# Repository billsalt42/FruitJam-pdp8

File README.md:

# PDP-8/E emulator for the Adafruit Fruit Jam

This turns an [Adafruit Fruit Jam](https://www.adafruit.com/product/6200) (RP2350B) into a
PDP-8/E minicomputer. It runs **OS/8** from RK05 cartridge-disk, DECtape or floppy images on the microSD card, or
the **TSS/8** time-sharing system with up to five users logged in at once. It also runs
two time-sharing systems built on OS/8, **MULTOS/8** and **ETOS**, if you supply their disk packs. TSS/8 comes in two
versions: DEC's TSS/8.24, and **UWM TSS/8.25** from the University of Wisconsin–Milwaukee, which
is assembled from source (see [`uwm/`](uwm/README.md)).
Output goes to an HDMI/DVI monitor as an 80×30 green-screen terminal. You type on a USB keyboard,
or connect from a computer over the USB-C serial ports.

```
Adafruit Fruit Jam PDP-8/E - OS/8 V3D - KBM V3Q - CCL V1F
Configured on 2026.09.24 at 17:53:24 PDT

Restart address = 07600

Type:
    .DIR                -  to get a list of files on DSK:
    .DIR SYS:           -  to get a list of files on SYS:
    .R PROGNAME         -  to run a system program
    .HELP FILENAME      -  to type a help file

.
```

## What is emulated

| Unit | Notes |
|---|---|
| PDP-8/E CPU, 32K words | Full instruction set, interrupts, KM8E memory extension (including user-mode traps) |
| KE8E EAE | Mode A and mode B (MUY, DVI, NMI, shifts, DAD, DST, DPIC, DCM, SAM, …) |
| KL8E console (03/04) | Keyboard and screen. The KSR mark bit is set on input. |
| RK8E + 4 × RK05 (74) | Disk images live on the microSD card. Uses the SIMH `.rk05` format, so PiDP-8/I and SIMH images work unchanged. |
| DK8-E line clock (13) | 60 Hz |
| LE8 line printer (66) | Output is appended to `printer.txt` on the SD card. |
| PC8E paper tape (01/02) | Reader input comes from `reader.bin` on the card; punch output is appended to `punch.bin`. |
| KL8E ×4 multiplexer (40–47) | TSS/8 terminals K01–K04. Each has its own virtual screen and USB serial port. |
| RF08 + RS08 (60–62, 64) | TSS/8 system disk (`tss8_rf.dsk`, 256K words). Blocks are cached in RAM and written back to the card. |
| TC08 + 4 × TU56 DECtape (76/77) | SIMH `.tu56` images (12-bit format). The tape moves with simulated acceleration and timing, block by block, as on the real drive. OS/8 can boot from DTA0. |
| RX8E + 2 × RX01 floppy (75) | SIMH `.rx01` images. An `.rx02` image switches to the RX28 controller (RX02 double density). OS/8 can boot from RXA0. |
| TSC8-75 (36) | The time-share board ETOS needs; fitted only while ETOS runs. |

The CPU is an independent C rewrite that follows SIMH's PDP-8 behaviour. It was checked against
SIMH with the same OS/8 and TSS/8 sessions and produced identical output (see [Testing](#testing)).

## What you need

* An Adafruit Fruit Jam
* A monitor or TV with HDMI input, and an HDMI cable
* A USB keyboard for one of the Fruit Jam's USB-A ports, or a computer running a terminal program
  on the USB-C port
* A microSD card formatted FAT32 or exFAT

## Quick start

1. **Flash the firmware.** Hold **Button 1** (BOOT) and tap **RESET**. A drive called `RP2350` appears.
   Copy `release/pdp8_fruitjam.uf2` onto it.
2. **Prepare the SD card.** Copy everything in the `sdcard/` folder to the root of the card:
   * `os8.rk05`: OS/8 V3D with BASIC, FORTRAN II/IV, PAL8, MACREL, TECO, U/W FOCAL, Adventure,
     BASIC games, Kermit-12 and more
   * `ock.rk05`: the OS/8 "Combined Kit" (V3D/V3F)
   * `blank.rk05`: an empty cartridge for your own files
   * `os8.tu56`: a bootable OS/8 V3F DECtape; `blank.tu56` and `blank.rx01`: an empty DECtape and floppy
   * `tss8_init.bin` and `tss8_rf.dsk`: DEC TSS/8.24 (the INIT loader tape and the RF08 system disk)
   * `uwm_init.bin` and `uwm_rf.dsk`: UWM TSS/8.25
   * `pdp8.cfg`: settings (optional)
3. Insert the card, connect the monitor and keyboard, and power up. During the 3-second countdown,
   press **O** for OS/8, **T** for DEC TSS/8 or **U** for UWM TSS/8. If you don't press anything, it boots the `system=`
   setting in `pdp8.cfg` (OS/8 out of the box). OS/8 comes up at the `.` prompt.

Updating from an earlier version: flash the new `.uf2`, and copy any `tss8_*`/`uwm_*`, `.tu56` or `.rx01` files you
don't have yet, plus the new `pdp8.cfg`, to the card. Your existing disk images keep working.

## Using it

| Key | Action |
|---|---|
| **F12** or **Button 1** | System menu: continue, boot OS/8 / TSS/8 / UWM TSS/8 / MULTOS/8 / ETOS, restart the OS/8 monitor at 07600, drives (I: swap disk, DECtape and floppy images, boot from tape or floppy), default system, keyboard case (K), speed, colour, save settings |
| **Alt-F1 … Alt-F5** | TSS/8: switch the monitor between the console (K00) and terminals K01–K04 |
| **F11** (or Alt-F6) | PDP-8/E front panel (lamps, switch register, console keys); F11 or Esc returns |
| Caps Lock | Toggles forced upper case (on by default, as on a Teletype; OS/8 commands must be upper case) |
| Backspace / Delete | RUBOUT (0177), which is OS/8's delete |
| Ctrl-C | Returns to the OS/8 monitor |
| Ctrl-O / Ctrl-U | Suppress output / delete the line |
| Arrow keys | VT52 cursor keys (ESC A/B/C/D) for TECO VTEDIT, KED, etc. |
| F1–F4 | VT52 PF1–PF4 |

**Serial ports:** the USB-C port shows up on your computer as **five** USB serial devices (for
example `/dev/ttyACM0`–`4`, `/dev/cu.usbmodem…`, or `COM` ports), named "PDP-8 Console K00" and
"TSS/8 Line K01"–"K04". Connect with any terminal program; the baud rate doesn't matter.
* The first port is the console. Everything on the console screen is copied to it, typing there
  works the same as on the keyboard, and **Ctrl-\\** opens the system menu.
* The other four are TSS/8 terminals K01–K04. They are only used while TSS/8 is running. Each one
  mirrors its virtual screen (Alt-F2 … Alt-F5), so several people can use TSS/8 from their own computers
  while someone else types on the Fruit Jam's keyboard.

**Screen:** the display is a VT52 with a few VT100 (ANSI) sequences added, so full-screen OS/8
editors work.

### A few things to try

```
.DIR                         list files on the system disk
.R BASIC                     BASIC  (NEW, give a name, type a program, RUN, BYE)
.EXECUTE HELLO.FT            compile and run a FORTRAN IV program (create it with EDIT or PIP)
.PAL PROG/L                  assemble PROG.PA with PAL8; .LOAD PROG / .START
.R UWF16K                    U/W FOCAL
.R FRTS  then  *ADVENT.LD<Esc>   Colossal Cave Adventure (press Enter at the three file prompts)
.R CHEKMO                    chess
.ZERO RKA1:                  initialise the first half of the disk in drive RK1 (blank.rk05)
.ZERO RKB1:                  ...and the second half
.COPY RKA1:<*.BA             copy files onto it
```

On OS/8 each RK05 cartridge appears as two devices: RKAn and RKBn for drive *n*.

### DECtapes and floppies

OS/8 sees the DECtape drives as **DTA0** and **DTA1** and the first floppy drive as **RXA0**. The
card comes with `os8.tu56` on DTA0 (a bootable OS/8 V3F system tape), a blank tape on DTA1 and a
blank floppy on RXA0:

```
.DIR DTA0:                   list the system tape
.ZERO DTA1:                  initialise the blank tape (also: ZERO RXA0:)
.COPY DTA1:<*.BA             copy files to it
.COPY RXA0:<DTA0:PIP.SV      ...or from tape to floppy
```

**F12 → I** (Drives) shows every drive. Keys 0–3 change RK0–RK3, 4–7 change DTA0–DTA3 and
8–9 change RXA0–RXA1. **N** in the image list makes a new blank `.tu56` or `.rx01` file. **B** boots
OS/8 from the DECtape in DTA0 and **F** from the floppy in RXA0. The choice is remembered for
**O**, and **W** saves it as `os8_boot`. DECtape images from SIMH, the PiDP-8/I project and
bitsavers (12-bit `.tu56`/`.dt8` format) work as they are. 16- and 18-bit DECtape images (from
PDP-11 or PDP-10 conversions) are not supported.

Tapes are read and written a block at a time. The block being worked on is written back when the
tape stops, and at least once a second.

### TSS/8

TSS/8 is DEC's time-sharing system for the PDP-8. It runs several users at once, each with their own
BASIC, FOCAL, FORTRAN, editor and files. To start it:

1. Press **T** at the boot countdown, or choose **T** in the F12 menu.
2. The console asks `LOAD, DUMP, START, ETC?`. Type `START`.
3. Enter the date as `M-D-YY` and the time as `HH:MM`, for example `9-25-84` and `09:35`. TSS/8.24
   only accepts years from 1974 to 1984, so pick a year in that range.
4. On any terminal, press Enter and then log in with `LOGIN 2 LXHE` (account 2, password LXHE).

```
.LOGIN 2 LXHE
TSS/8.24  JOB 01  [00,02]  K01    09:35:04
.SYSTAT                     who is logged in, free core and disk
.R CAT                      list your files
.R BASIC                    BASIC  (NEW / OLD, RUN, SAVE, BYE)
.R FOCAL                    FOCAL  (answer YES to keep LOG/EXP/ATN)
.R EDIT, .R FORT, .R PALD   editor, FORTRAN, PAL-D assembler
^B S                        stop the running program (Ctrl-B, then S)
.LOGOUT
```

**UWM TSS/8** is started the same way (press **U**). Two differences: it only lets you log in
with a **Ctrl-B** in front of `LOGIN`, and it prints a message of the day. See
[`uwm/README.md`](uwm/README.md) for how it was built and what was changed.

Switch between the console and K01–K04 with **Alt-F1 … Alt-F5**, or use the extra USB serial ports.
Five people can be logged in at once. The RF08 disk is cached in RAM and written back to
`tss8_rf.dsk` about once a second, so let it settle (LED off) before you power off. Keep a copy of the
original `tss8_rf.dsk` if you want to be able to start over.

### MULTOS/8

[MULTOS/8](http://www.pdp8online.com/) (Computer Methods, Salt Lake City, 1979) is time-sharing
built on OS/8. Each user runs ordinary OS/8 and its programs (BASIC, FOCAL,
PAL8, TECO and the rest), and has a slice of the RK05 as their own disk. It is not part of this
project, so get `multos8.rk05` from pdp8online.com and copy it to the card.

1. Press **M** at the boot countdown or in the F12 menu (or set `system=multos`). OS/8 boots
   from the MULTOS pack.
2. Recommended once: `COPY J2:<LOGOFF.SV,SYSTAT.SV,TIME.SV,TALK.SV`. This gives the second
   user their own copies of the MULTOS utilities, so `R LOGOFF` works for them.
3. `DATE 12-OCT-77` (OS/8 V3D only knows 1970–77), then `R MULTOS`, then the time as `hhmm`.
4. **Ctrl-H** logs on, on the console and on terminal K01 (Alt-F2, the second USB serial port,
   or SSH). `R LOGOFF` signs off; over SSH it also ends the session.

The pack as distributed is built for two terminals: the console, and K01 on the multiplexer at
device 40. In its `PARAM.PG`, `TERM2 EQU 32` means *octal* 40, because the PAGE8 assembler
reads plain numbers as decimal. Its clock shows a time a few hours on from the one you enter,
and runs slow. SIMH does exactly the same with this pack, so it comes from the software, not the
emulator. `tests/multostest.py` runs MULTOS/8 on the desktop build (set `MULTOS_RK`). It logs on
two users at once, runs BASIC on K01 while the console runs SYSTAT, and checks logging off and
SSH.

### ETOS

[ETOS](https://www.pdp8online.com/os/etos/etos.shtml) (Educational Data Systems, V5B 1978) gives
every user a virtual PDP-8 running unmodified OS/8. User programs run in the KM8-E's user mode, and
the monitor emulates their I/O. It also needs the **TSC8-75** time-share board, which traps JMP
and JMS in user mode so ETOS can follow field changes. The emulator has that board (after SIMH's
TSC device) and switches it on only for ETOS. Get `etosv5b-demo.rk05` from pdp8online.com and copy
it to the card.

1. Press **E** at the boot countdown or in the F12 menu (or set `system=etos`). OS/8 boots from
   the ETOS pack.
2. `R ETOS`, then answer `T` to `OPTION?` to start the time-sharing.
3. On the console and on K01 (Alt-F2, the second USB serial port, or SSH), press Enter for
   `?LOGIN PLEASE`, then type `LOGIN`. The demo's accounts are `0,4` (password `USER1`,
   privileged) and `0,5` (`USER2`).
4. `^V S` Enter gives the ETOS monitor's `!` prompt, for commands such as `SYSTAT` and `LOGOUT`.
   Over SSH, `LOGOUT` also ends the session. If you just close the window, the Fruit Jam logs the
   job out (Ctrl-C, `^V S`, `LOGOUT`).

The demo pack is configured for two terminals, the console and K01. Typing on K02–K04 hangs
it, on SIMH too, so leave `etos_lines=1`. Its clock isn't set, so it shows 1 January 1975.
`tests/etostest.py` (set `ETOS_RK`) logs in two users, runs BASIC golf on K01 while the console runs
its own BASIC program and SYSTAT, and checks LOGOUT and SSH. The same steps give the same output
on SIMH with `set tsc enabled`.

### Front panel

Press **F11** for a PDP-8/E-style front panel. The machine keeps running while you watch it.

* **Lamps:** EMA + MEMORY ADDRESS (15 lamps), a 12-bit register display, and RUN and ION. The
  **Up/Down** keys turn the selector to STATUS, AC (with the link lamp), MD, MQ or IR. While the
  panel is on screen, the CPU samples its registers every few dozen instructions. Each lamp's
  brightness follows how often it was lit, and fades a little like an incandescent bulb, so the
  familiar idle-loop and swapping patterns show up.
* **Switch register:** the number-row keys **1 2 3 … 9 0 - =** flip switches 0–11. **O** followed by
  four octal digits sets them all at once, and **Z** clears them. Programs read the switches with
  `OSR`.
* **Console keys:** **H** HALT, **G** CONT, **S** SING STEP, **L** ADDR LOAD (PC and console address
  ← switches), **X** EXTD ADDR LOAD (IF ← switches 6–8, DF ← 9–11), **E** EXAM, **D** DEP (store the
  switches and advance) and **C** CLEAR. Like the real console, EXAM/DEP/ADDR LOAD/CLEAR/SING STEP
  only work while the machine is halted.

Toggling in a program the 1970s way looks like this. Press H, then O0200 and L to set the address.
Then, for each word, O and four octal digits followed by D to deposit it. Finally O0200, L and G to
run it.

### Terminals over WiFi (SSH)

The Fruit Jam's ESP32-C6 WiFi coprocessor lets people log in to the PDP-8 with an ordinary `ssh`
client, from Mac, Linux or Windows. Under TSS/8 each SSH login gets one of the terminal lines
K01–K04, so up to four people can share the machine over the network. Under MULTOS/8 and ETOS it
gets one of the lines they were built for. Under OS/8 it gets the console.

1. In `PDP8.CFG` set `wifi_ssid`, `wifi_password` and `ssh_password` (all SSH users share this one
   password), and restart.
2. The F12 menu shows the address, for example `SSH: WiFi "home": ssh 192.168.1.40`, and the host key
   fingerprint. The first time you connect, `ssh` shows the same fingerprint and asks you to confirm it.
3. `ssh 192.168.1.40`, then enter the SSH password. You'll see
   `[PDP-8 on Fruit Jam: connected to line K02 of TSS/8]`. Press Enter and log in to TSS/8 as usual,
   for example `LOGIN 2 LXHE`, or `^B LOGIN 2 LXHE` under UWM.

The SSH user name picks the line: `k01` … `k04` for a particular TSS/8 line, `k00` (or `console`)
for the console, and anything else for the first free line. A line whose USB serial port is open
counts as busy. TSS/8's `LOGOUT` ends the SSH session, like a modem hanging up. If you just close the
window instead, the Fruit Jam logs that job out for you (`^B S`, then `LOGOUT`) so the next person
on that line starts fresh.

The server only speaks the modern algorithms all current clients use: curve25519 key exchange, an
Ed25519 host key, and chacha20-poly1305 encryption. It runs on the Fruit Jam's main processor, and
the WiFi chip only carries the network connections, so its standard nina-fw firmware is used as it
comes. The host key is created on first use and kept in `SSHKEY.BIN` on the card. Delete that
file to make a new key. TSS/8's own passwords are 1970s-grade, so keep this on your home
network, not open to the internet.

### PiDP-8/I hardware panel

A real [PiDP-8/I](https://obsolescence.dev/pidp8i) panel can be connected too. A Raspberry Pi Pico 2
(or Pico) takes the place of the Raspberry Pi behind the panel and plugs into one of the Fruit Jam's
USB-A ports. Its lamps and switches then work with OS/8 and TSS/8, alongside the F11 screen. See
[`pidp8-panel/README.md`](pidp8-panel/README.md) for the wiring, firmware and switch functions. To
avoid the 26 jumper wires, [`hardware/pico-adapter`](hardware/pico-adapter/README.md) has a ready-to-order
adapter board (KiCad project and gerbers).

### Settings (`pdp8.cfg`)

```
system=os8          # what to boot at power-up: os8, tss8, uwm, multos or etos
rk0=os8.rk05        # disk images for drives 0-3 (files in the root of the card)
rk1=blank.rk05
rk2=ock.rk05
rk3=
dt0=os8.tu56        # TC08 DECtape images for DTA0-DTA3
dt1=blank.tu56
dt2=
dt3=
rx0=blank.rx01      # floppy images for RXA0-RXA1 (.rx01, or .rx02 for the RX28)
rx1=
os8_boot=rk         # OS/8 boots from rk (RK0), dectape (DTA0) or floppy (RXA0)
tss8_bin=tss8_init.bin   # TSS/8 INIT tape (BIN format)
tss8_rf=tss8_rf.dsk      # TSS/8 RF08 disk image (SIMH format)
uwm_bin=uwm_init.bin     # UWM TSS/8.25 INIT tape
uwm_rf=uwm_rf.dsk        # UWM TSS/8.25 RF08 disk image
color=green         # green, amber, white, blue
uppercase=on        # fold keyboard input to upper case
speed=full          # full = as fast as the RP2350 can go; real = ~400K instr/s like an 8/E
autoboot=3          # seconds before booting; -1 waits for Enter
wifi_ssid=          # WiFi network for SSH (empty = WiFi off)
wifi_password=
ssh_password=       # the one password for SSH logins (SSH stays off while empty)
ssh_port=22
hostname=pdp8       # name the Fruit Jam gives the WiFi router
multos_rk=multos8.rk05   # MULTOS/8 pack, booted with M (not included)
multos_lines=1      # terminals besides the console that MULTOS/8 was built for
etos_rk=etosv5b-demo.rk05   # ETOS pack, booted with E (not included)
etos_lines=1        # terminals besides the console that ETOS was configured for
```

Values can't contain `#`, because everything after it is treated as a comment.

You can change all of these from the F12 menu, and **W** in that menu writes them back to the card.
If `os8.rk05` is missing, the first `*.rk05` file on the card is booted. An image shorter than a
full RK05 (for example one produced by SIMH) is padded with zeros to 3,325,952 bytes the first time
it is mounted.

Writes go straight to the image file on the card, and the file is synced after half a second without
disk activity. The on-board LED (GPIO29) lights while there are unsynced writes. Wait for it to go out before you
switch off.

## How it works

```
core 0: PDP-8/E CPU + devices ─ RK8E / RF08 ─► FatFs ─► SPI microSD (GPIO34-36, CS 39)
        TinyUSB host (PIO-USB, GPIO1/2, via the on-board hub) ─► keyboard
        TinyUSB device (native USB-C) ─► 5 CDC serial ports (K00-K04)
        5 virtual terminals (VT52/ANSI), one per PDP-8 terminal line
core 1: HSTX DVI 640x480@60 (GPIO12-19), scanlines rendered on the fly
        from the selected terminal's 80x30 character buffer with an 8x16 font
```

The clocks follow the approach of the Adafruit/Pimoroni DVHSTX driver. The system runs at 240 MHz
from the USB PLL, an exact multiple of 12 MHz, which PIO-USB needs. The system PLL is free to make the
exact 126 MHz HSTX clock (25.2 MHz pixels). The whole program runs from RAM (`copy_to_ram`).

```
core/        portable PDP-8/E emulator (pdp8.c/.h); no hardware dependencies
firmware/    Fruit Jam firmware (Pico SDK): main, video, terminal, front panel, keyboard, SD card, USB,
             PiDP-8/I panel link
pidp8-panel/ firmware for the Pico 2 / Pico that drives a PiDP-8/I panel, wiring guide, test tool
net/         SSH server (ssh.c), SSH sessions as terminal lines (sshsrv.c), ESP32 nina-fw driver
             (nina.c) and WiFi/listener state machine (wifi.c); portable, also used by the host build
hardware/    pico-adapter: PiDP-8/I <-> Pico adapter board (KiCad 7 project, gerbers, generator scripts)
lib/monocypher  Monocypher 4.0.3 (X25519, Ed25519, ChaCha20, Poly1305)
host/        Linux/macOS command-line build of the same core, used for testing
lib/         Pico-PIO-USB (MIT)
sdcard/      disk images + sample config for the microSD card
tests/       comparison tests against SIMH, and the UWM TSS/8 functional test
tools/       font converter, OS/8 image build script, palbart PDP-8 assembler
uwm/         UWM TSS/8.25 sources, patches and the script that builds uwm_rf.dsk
```

## Building from source

Firmware (needs Pico SDK 2.2 or newer, which has the `adafruit_fruit_jam` board, plus
`arm-none-eabi-gcc`):

```sh
git clone https://github.com/raspberrypi/pico-sdk
git -C pico-sdk submodule update --init lib/tinyusb
export PICO_SDK_PATH=$PWD/pico-sdk
make firmware            # -> pdp8_fruitjam.uf2
make panel               # -> pidp8_panel_pico2.uf2, pidp8_panel_pico.uf2 (PiDP-8/I interface)
```

Desktop build of the emulator, for trying OS/8 or TSS/8 in a terminal (Ctrl-E quits):

```sh
make host
cp sdcard/os8.rk05 /tmp/ && build/pdp8host /tmp/os8.rk05
cp sdcard/tss8_rf.dsk /tmp/ && build/pdp8host -tss8 /tmp/tss8_rf.dsk sdcard/tss8_init.bin 4000
#   ...then connect extra TSS/8 terminals with:  nc localhost 4000   (or telnet)
```

Rebuild the OS/8 disk images from the original DEC distribution DECtapes (this uses the PiDP-8/I
project's tools and SIMH): `tools/build-images.sh`. Rebuild UWM TSS/8 from its sources:
`make uwm`.

## Testing

`make test` runs the same scripted OS/8 and TSS/8 sessions on SIMH and on this core and compares the
transcripts. It needs a SIMH `pdp8` binary in `SIMH_PDP8` and Python `pexpect`. The sessions
cover:

* `DIR`, PIP file creation, CCL commands
* FORTRAN IV compile, load and run (`EXECUTE`), including trig, exp/log and integer loops
* PAL8 assembly, `LOAD` and `START` of the resulting program
* BASIC with floating-point functions and arrays, plus `SAVE`
* U/W FOCAL (interrupt-driven terminal I/O)
* `tests/eaetest.pa`: an EAE exerciser that checksums 512 random operand pairs through every
  mode A and mode B instruction
* TSS/8 (`tests/tss8test.py`): INIT start-up, date and time, login, `R CAT`, a BASIC prime sieve,
  FOCAL, `SYSTAT` and `LOGOUT` on the console. This exercises the RF08 disk, user-mode traps,
  swapping and the clock.

* PiDP-8/I panel logic (`tests/pidptest.c`, `make pidptest`). A program is toggled in and run
  from simulated switches (LOAD ADD, DEP, EXAM, START, STOP, SING INST + CONT). The test also checks
  the lamp frames, both halted and averaged while running, and the protocol's resynchronisation.
* SSH (`tests/sshtest.py`, `make sshtest`). These run DEC TSS/8.24 with real SSH clients: OpenSSH,
  plus asyncssh and Dropbear's `dbclient` when installed. They check the host key fingerprint and
  that three wrong passwords end the connection. Four sessions log in on K01–K04 and run BASIC at
  the same time, and a fifth is turned away. They also check that `k00` gets the console, that a
  long paste is flow-controlled without loss, and that `LOGOUT` hangs up. A dropped session's job
  must be logged out, the session must survive forced re-keying, and 30 connections of random
  junk must not stop the server accepting logins. Under OS/8, SSH must get the console. The
  same tests run a second time with the SSH traffic going through the nina-fw driver to a
  simulated ESP32 (`tests/fakeesp.c`). That simulation answers each command exactly as nina-fw's
  `CommandHandler.cpp` does, and rejects malformed command packets.
* DECtape and floppy (`tests/dtrxtest.py`). OS/8 on the RK05 zeroes a blank tape and a blank floppy,
  copies files to and between them, types and runs files from them, then deletes and SQUISHes on
  the tape. The transcripts match SIMH's, and so do the resulting tape and floppy images, byte for
  byte. OS/8 is also booted from a DECtape system tape and runs BASIC from it. The RX28/RX02 code is
  ported from SIMH line for line, but no RX02 OS/8 system was available to test it.
* UWM TSS/8.25 (`tests/uwmtest.py`). SIMH can't run this monitor unmodified (see
  [`uwm/README.md`](uwm/README.md)), so this is a functional test. It covers start-up, Ctrl-B login on
  the console and all four lines, the message of the day, BASIC on four lines at once, SYSTAT showing
  all five jobs, CAT, FOCAL and LOGOUT.

Except for the UWM test, all of these give identical output on SIMH and on this core. On the desktop build, all five TSS/8 terminals
(the console plus four multiplexer lines) were also logged in at once, with four of them running BASIC
programs at the same time.
Adventure, CHEKMO, a second RK05 drive
(`ZERO`/`COPY`/`DIR RKA1:`) and the OS/8 Combined Kit image were also run on the desktop build.

**Hardware status:** v1.0 (OS/8), v1.1 (DEC TSS/8, virtual terminals, extra USB serial ports) and
v1.2 (UWM TSS/8, paper tape) have been run on a real Fruit Jam. v1.3 adds the front panel. The
panel's drawing and console keys were checked on the desktop build, which produced the screenshot
above. It compiles cleanly for the RP2350 (about 117 KB of code and 162 KB of RAM) but has not yet
been run on the board. v1.4 adds the PiDP-8/I link. As of v1.4.2 it has been run on a real Fruit Jam
with an original Pico driving a PiDP-8/I panel, and its switch and lamp logic is also covered by
`pidptest`.
v1.5 adds SSH over WiFi, which has been run on a real Fruit Jam with UWM TSS/8 and SSH sessions
on all four terminal lines. v1.6 adds MULTOS/8 and v1.7 adds ETOS with the TSC8-75; both have also
been run on the board. v1.8 adds DECtape and floppy drives, tested on the desktop build against
SIMH; the firmware builds but hasn't been run on the board yet.

## Licences

* Emulator, firmware and tools: MIT. The CPU and device semantics follow SIMH (Robert M Supnik,
  MIT-style licence).
* HSTX DVI code: derived from pico-examples (BSD-3-Clause).
* Pico-PIO-USB: MIT. FatFs: ChaN's FatFs licence (see `firmware/fatfs/LICENSE.txt`).
* Monocypher (`lib/monocypher`): CC0 or BSD-2-Clause, your choice (`lib/monocypher/LICENCE.md`).
* Font: Spleen 8x16 by Frederic Cambus, BSD-2-Clause (`firmware/FONT-LICENSE-spleen.txt`).
* OS/8 and its utilities are DEC software, distributed under the DEC hobbyist licence in
  `sdcard/OS8-LICENSE.md` (non-commercial use). The disk images were built with the
  [PiDP-8/I](https://tangentsoft.com/pidp8i) project's tools.
* UWM TSS/8.25 sources: DEC TSS/8 as extended at the University of Wisconsin–Milwaukee
  (Richard Bartlein, 1974–76), from bitsavers and Brad Parker's cpus-pdp8 project. `uwm_rf.dsk`
  carries the DEC TSS/8.24 library file system. palbart (`tools/palbart`) is free software; its
  licence is included with it.
* The TSS/8.24 files (`tss8_init.bin`, `tss8_rf.dsk`) are the SIMH TSS/8 kit as redistributed by
  the PiDP-8/I project. That project describes their licensing as not fully settled but believed
  freely redistributable for hobby use (see its `COPYING.md`).

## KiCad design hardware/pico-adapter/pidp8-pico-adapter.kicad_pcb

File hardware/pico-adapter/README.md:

# PiDP-8/I ↔ Raspberry Pi Pico adapter board

This board replaces the 26 jumper wires between a PiDP-8/I and the Pico panel interface. It is
the size of a Raspberry Pi HAT (65 × 56.5 mm), with the Pi's four M2.5 mounting holes. Its
40-pin connector sits where the Pi's GPIO header would be, so it plugs into the PiDP-8/I exactly
where the Raspberry Pi did. The Pico (or Pico 2) is soldered to the **back**. Its USB connector
sticks out at one edge for the cable to the Fruit Jam, and its BOOTSEL button stays reachable.

| File | What it is |
|---|---|
| `pidp8-pico-adapter-gerbers.zip` | upload this to JLCPCB, PCBWay, OSH Park, etc. |
| `pidp8-pico-adapter-1to1.pdf` | print at 100 % to check the fit before ordering |
| `pidp8-pico-adapter-schematic.pdf` | schematic |
| `pidp8-pico-adapter.kicad_pcb` / `.kicad_sch` / `.kicad_pro` | KiCad 7 project, if you want to change it |
| `make_board.py`, `route.py`, `render.py`, `make_schematic.py`, `check_board.py` | the scripts that generate everything |

## Ordering

These are standard settings everywhere: 2 layers, 1.6 mm, any colour, HASL finish. The smallest
features are 0.25 mm tracks with 0.2 mm spacing and 0.35 mm vias, well within every cheap service.
At JLCPCB, five boards cost a few dollars plus shipping.

## Parts

| Ref | Part |
|---|---|
| J1 | 2×20 header, 2.54 mm. Use what a Raspberry Pi would present: normally a **male** pin header (the PiDP-8/I has the socket). If your PiDP-8/I has pins instead, use a 2×20 female socket. |
| U1 | Raspberry Pi Pico, Pico 2 (or the W versions), with two 1×20 male headers, or soldered flat by its castellations |
| JP1, JP2 | solder bridges (no parts) |
| — | 4 × M2.5 standoffs, as for the Pi (optional) |

## Assembly

1. **Jumpers first.** On the front, bridge the middle pad of JP1 and JP2 with a blob of solder:
   * to **STD** for a normal PiDP-8/I,
   * to **SER** if your PiDP-8/I has the serial-port modification (columns 10 and 11 then come
     from header pins 5 and 3 instead of 10 and 8; see `pidp8-panel/README.md`).

   Never bridge all three pads.
2. **J1 on the front** (the side with the jumpers and the big title). It faces the PiDP-8/I.
   Solder it on the back.
3. **The Pico on the back.** Match the silkscreen outline, with the USB connector at the board
   edge. Pin 1 is at the corner with the bevel. Solder on the front.
4. Flash `pidp8_panel_pico.uf2` or `pidp8_panel_pico2.uf2` (v1.2 or later), then plug the board
   into the PiDP-8/I in place of the Raspberry Pi. Don't fit both at once.

## How the firmware knows

The board ties the Pico's **GP28 to ground**. At start-up the panel firmware sees that and uses
this board's GPIO assignment, recorded in `pidp8-panel/board_map.h`. With GP28 left open, as when
hand-wired, it uses the original table from the panel README. One firmware file works both ways.

Each matrix line on the board goes to whichever Pico GPIO sits closest to its header pin, so the
tracks hardly cross. `make_board.py` makes that choice and writes `board_map.h` at the same time,
so the board and the firmware can't disagree. `check_board.py` then follows every connection on
the finished board, through the jumpers, and compares it with the PiDP-8/I's wiring as the pidp8i
software defines it and with `board_map.h`.

## Status

The board was generated, autorouted (Freerouting) and checked by script:
* KiCad's DRC reports no errors and no unconnected items. The only warnings are cosmetic: the Pico
  outline's USB tab overhangs the edge, and the footprints are generated rather than taken from a
  library.
* `check_board.py` passes.
* The gerbers were re-rendered with gerbv to confirm they are complete.

**It has not been built yet.** Before ordering, print the 1:1 PDF and hold it against the PiDP-8/I.
Check that the 40-pin connector lines up with its socket and that the mounting holes match. Also
check that nothing on the PiDP-8/I side gets in the way of the board where the Pi used to be.

## Regenerating

```sh
FREEROUTING_JAR=/path/to/freerouting-1.9.0.jar python3 route.py
```

This needs KiCad 7 (its `pcbnew` Python module and `kicad-cli`), Java 17+,
[Freerouting](https://github.com/freerouting/freerouting) 1.9, plus scipy, cairosvg and Pillow.
`xvfb-run` is used automatically on a headless machine. If you change the GPIO assignment,
rebuild the panel firmware (`make panel`) so it picks up the new `board_map.h`.

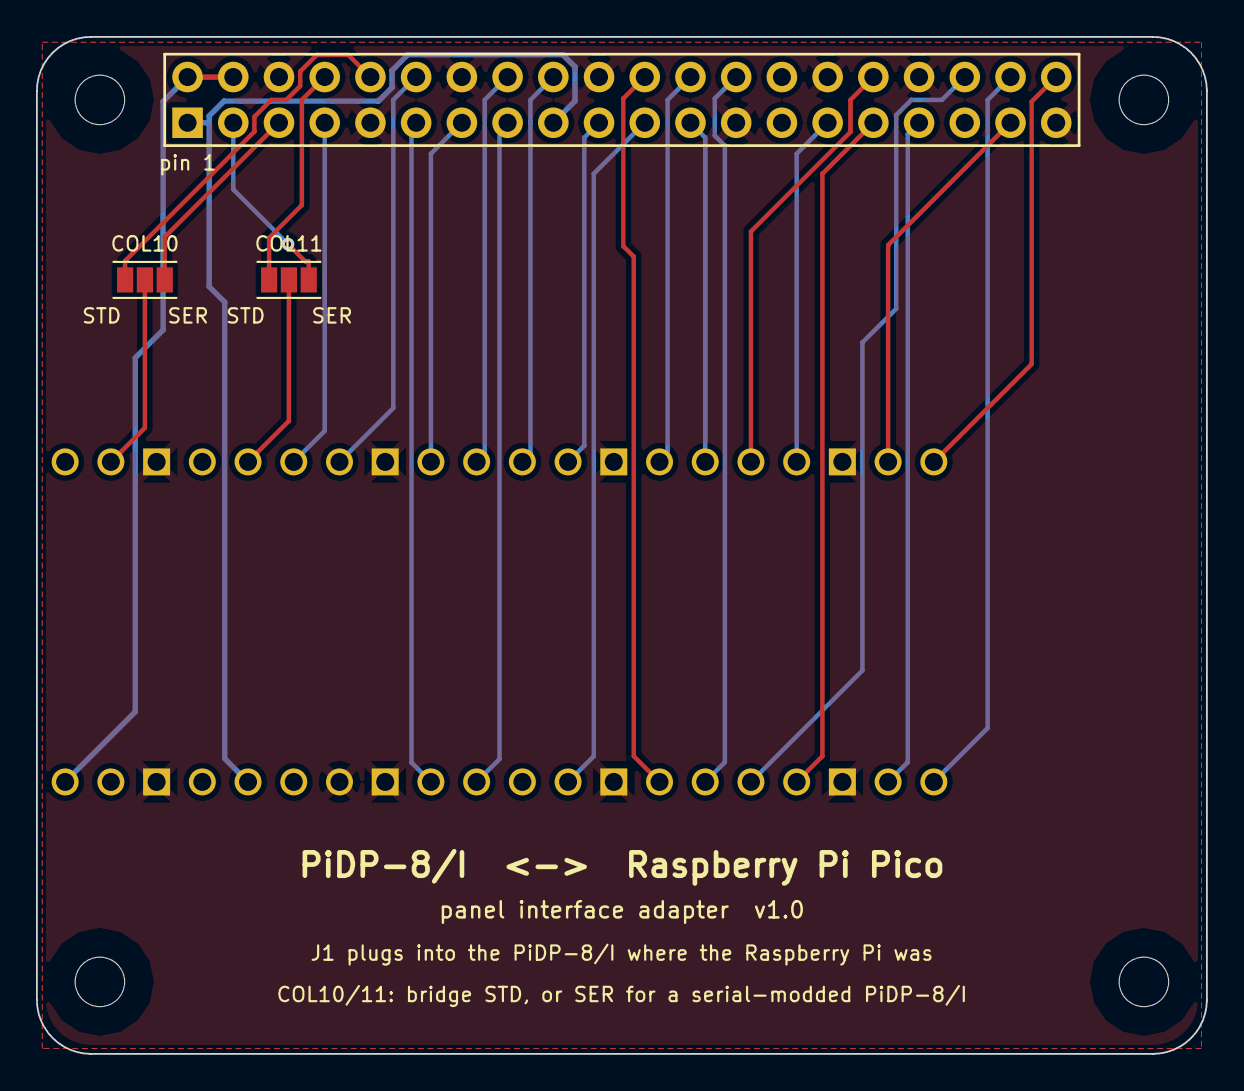
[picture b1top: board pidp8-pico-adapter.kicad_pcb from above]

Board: 2 copper layers, 65.0 x 56.5 mm, 8 parts (1 on the bottom side), 30 nets.

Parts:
H1, H2, H3, H4: M2.5
J1: PiDP-8/I
JP1, JP2: STD-SER
U1: Raspberry Pi Pico

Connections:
+3V3: J1.1, J1.17, U1.36
+5V: J1.2, J1.4, U1.40
COL0: J1.33, U1.22
COL1: J1.32, U1.16
COL2: J1.23, U1.15
COL3: J1.19, U1.12
COL4: J1.21, U1.29
COL5: J1.24, U1.14
COL6: J1.26, U1.26
COL7: J1.31, U1.24
COL8: J1.29, U1.17
COL9: J1.7, U1.6
COL10_PICO: JP1.2, U1.2
COL10_SER: J1.5, JP1.3
COL10_STD: J1.10, JP1.1
COL11_PICO: JP2.2, U1.5
COL11_SER: J1.3, JP2.3
COL11_STD: J1.8, JP2.1
GND: J1.6, J1.9, J1.14, J1.20, J1.25, J1.30, J1.34, J1.39, U1.3, U1.8, U1.13, U1.18, U1.23, U1.28, U1.33, U1.34, U1.38
LROW0: J1.38, U1.21
LROW1: J1.40, U1.20
LROW2: J1.15, U1.31
LROW3: J1.16, U1.10
LROW4: J1.18, U1.11
LROW5: J1.22, U1.27
LROW6: J1.37, U1.19
LROW7: J1.13, U1.9
SROW0: J1.36, U1.25
SROW1: J1.11, U1.32
SROW2: J1.12, U1.7
